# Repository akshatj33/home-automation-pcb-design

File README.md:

# home-automation-pcb-design
This is a board layout and schematic for home automation

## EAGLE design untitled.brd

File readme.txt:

This is a board layout and pcb design which I created for home automation on Eagle CAD platform.
It has 6 PWM pins to control the speed of 6 Fans and two shift registers to controll 16 lights.
The microcontroller used is ATMEGA328 which is basically arduino UNO.
The PCB has connections for bluetooth module so that the device can be controlled through a mobile app.

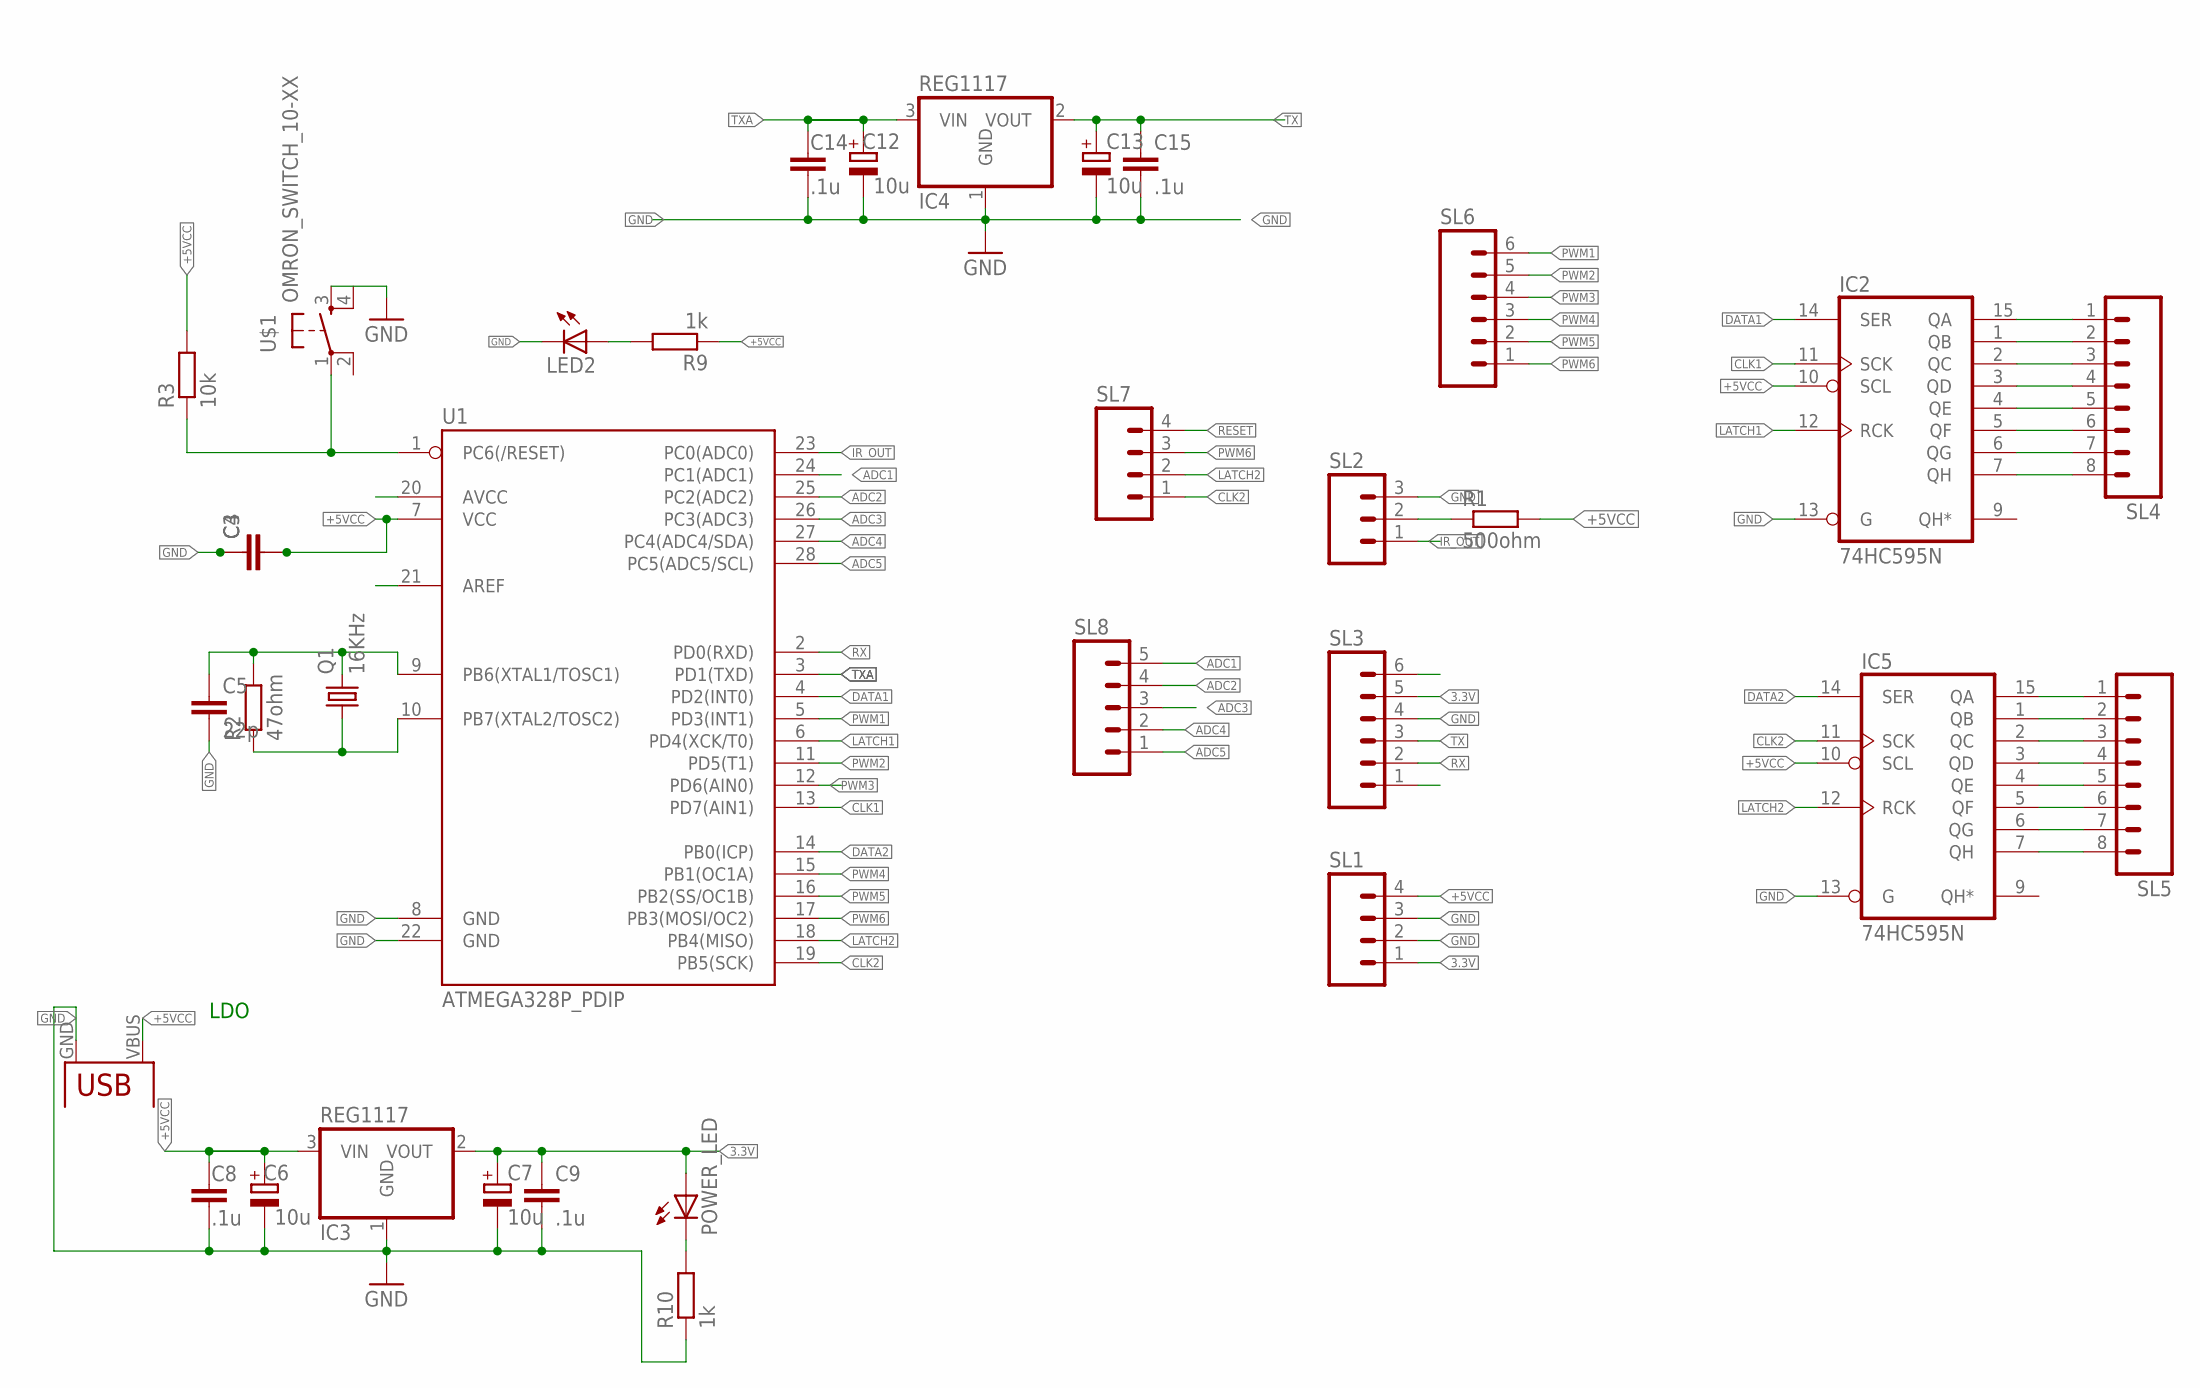
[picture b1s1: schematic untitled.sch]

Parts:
C3, C4: C-EU025-025X050; C025-025X050
C5: 22p; C025-025X050
C6, C7, C12, C13: 10u; E2,5-5
C8, C9, C14, C15: .1u; C025-025X050
IC2, IC5: 74HC595N; DIL16
IC3, IC4: REG1117; SOT223
LED2: LED3MM
POWER_LED: LED3MM
Q1: 16KHz; TC26H
R1: 500ohm; 0207/7
R2: 47ohm; 0207/7
R3: 10k; 0207/7
R9: 1k; 0207/10
R10: 1k; 0207/7
SL1, SL7: M04; 04P
SL2: M03; 03P
SL3, SL6: M06; 06P
SL4, SL5: M08; 08P
SL8: M05; 05P
U1: ATMEGA328P_PDIP; DIL28-3
U$1: OMRON_SWITCH_10-XX; B3F-10XX
U$2: USB(POWER)

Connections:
3.3V: C7.+, C9.1, IC3.2 (VOUT), POWER_LED.A, SL1.1, SL3.5
+5VCC: C3.2, C4.2, C6.+, C8.1, IC2.10 (SCL), IC3.3 (VIN), IC5.10 (SCL), R1.2, R3.2, R9.1, SL1.4, U1.7 (VCC), U$2.VBUS (VCC)
ADC1: SL8.5, U1.24 (PC1(ADC1))
ADC2: SL8.4, U1.25 (PC2(ADC2))
ADC3: SL8.3, U1.26 (PC3(ADC3))
ADC4: SL8.2, U1.27 (PC4(ADC4/SDA))
ADC5: SL8.1, U1.28 (PC5(ADC5/SCL))
CLK1: IC2.11 (SCK), U1.13 (PD7(AIN1))
CLK2: IC5.11 (SCK), SL7.1, U1.19 (PB5(SCK))
DATA1: IC2.14 (SER), U1.4 (PD2(INT0))
DATA2: IC5.14 (SER), U1.14 (PB0(ICP))
GND: C3.1, C4.1, C5.2, C6.-, C7.-, C8.2, C9.2, C12.-, C13.-, C14.2, C15.2, IC2.8 (GND), IC2.13 (G), IC3.1 (GND), IC4.1 (GND), IC5.8 (GND), IC5.13 (G), LED2.K (C), R10.1, SL1.2, SL1.3, SL2.3, SL3.4, U1.8 (GND), U1.22 (GND), U$1.3 (S), U$2.GND
IR_OUT: SL2.1, U1.23 (PC0(ADC0))
LATCH1: IC2.12 (RCK), U1.6 (PD4(XCK/T0))
LATCH2: IC5.12 (RCK), SL7.2, U1.18 (PB4(MISO))
unnamed: IC2.15 (QA), SL4.1
unnamed: R1.1, SL2.2
unnamed: LED2.A, R9.2
unnamed: IC2.1 (QB), SL4.2
unnamed: C5.1, Q1.2, R2.2, U1.9 (PB6(XTAL1/TOSC1))
unnamed: Q1.1, R2.1, U1.10 (PB7(XTAL2/TOSC2))
unnamed: POWER_LED.K (C), R10.2
unnamed: IC2.3 (QD), SL4.4
unnamed: IC2.2 (QC), SL4.3
unnamed: IC2.4 (QE), SL4.5
unnamed: IC2.5 (QF), SL4.6
unnamed: IC2.6 (QG), SL4.7
unnamed: IC2.7 (QH), SL4.8
unnamed: IC5.15 (QA), SL5.1
unnamed: IC5.1 (QB), SL5.2
unnamed: IC5.2 (QC), SL5.3
unnamed: IC5.3 (QD), SL5.4
unnamed: IC5.4 (QE), SL5.5
unnamed: IC5.5 (QF), SL5.6
unnamed: IC5.6 (QG), SL5.7
unnamed: IC5.7 (QH), SL5.8
PWM1: SL6.6, U1.5 (PD3(INT1))
PWM2: SL6.5, U1.11 (PD5(T1))
PWM3: SL6.4, U1.12 (PD6(AIN0))
PWM4: SL6.3, U1.15 (PB1(OC1A))
PWM5: SL6.2, U1.16 (PB2(SS/OC1B))
PWM6: SL6.1, SL7.3, U1.17 (PB3(MOSI/OC2))
RESET: R3.1, SL7.4, U1.1 (PC6(/RESET)), U$1.1
RX: SL3.2, U1.2 (PD0(RXD))
TX: C13.+, C15.1, IC4.2 (VOUT), SL3.3
TXA: C12.+, C14.1, IC4.3 (VIN), U1.3 (PD1(TXD))
VCC: IC2.16 (VCC), IC5.16 (VCC)

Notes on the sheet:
LDO

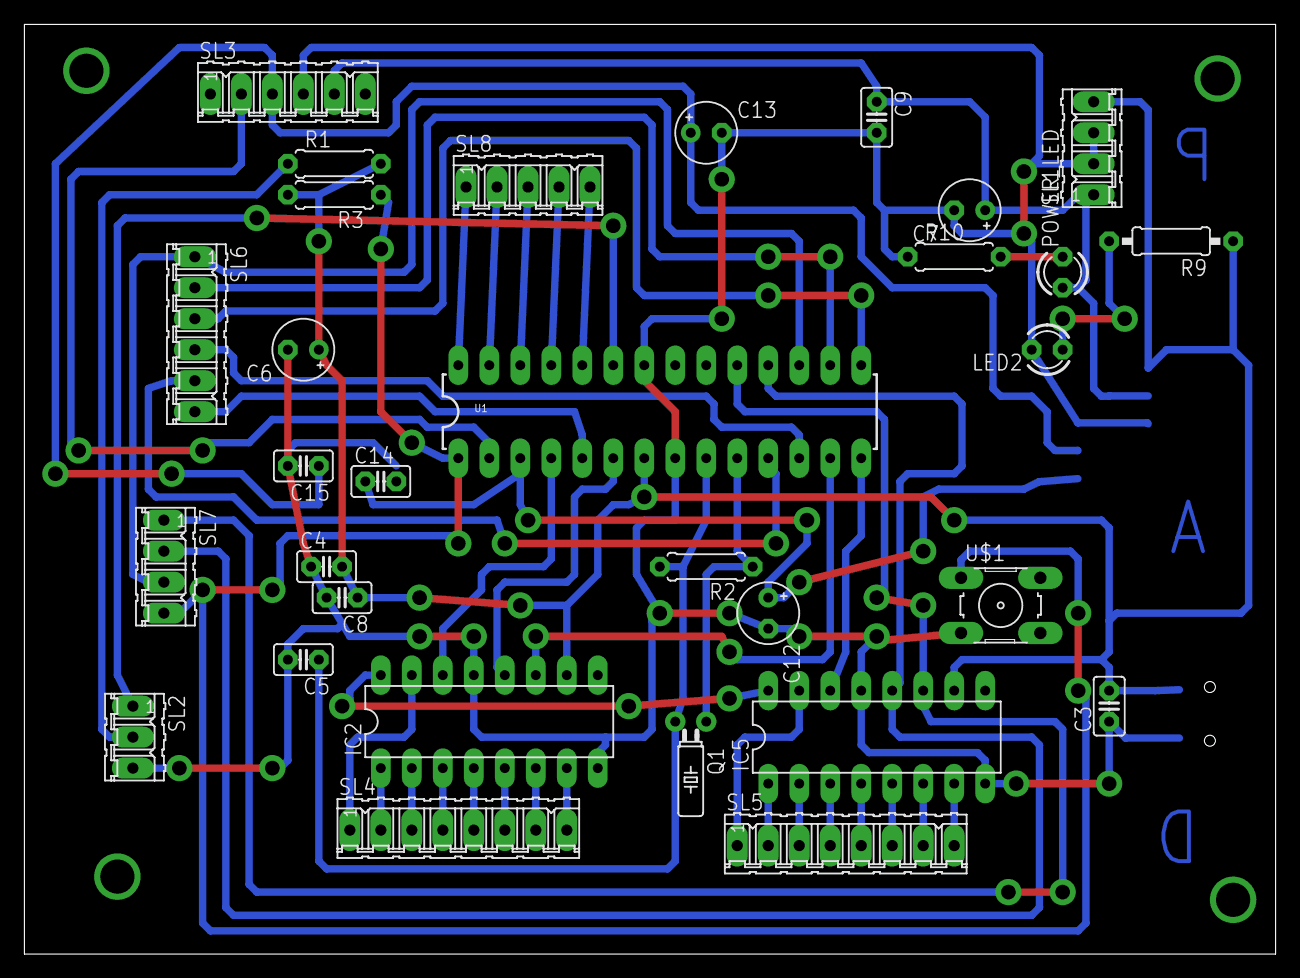
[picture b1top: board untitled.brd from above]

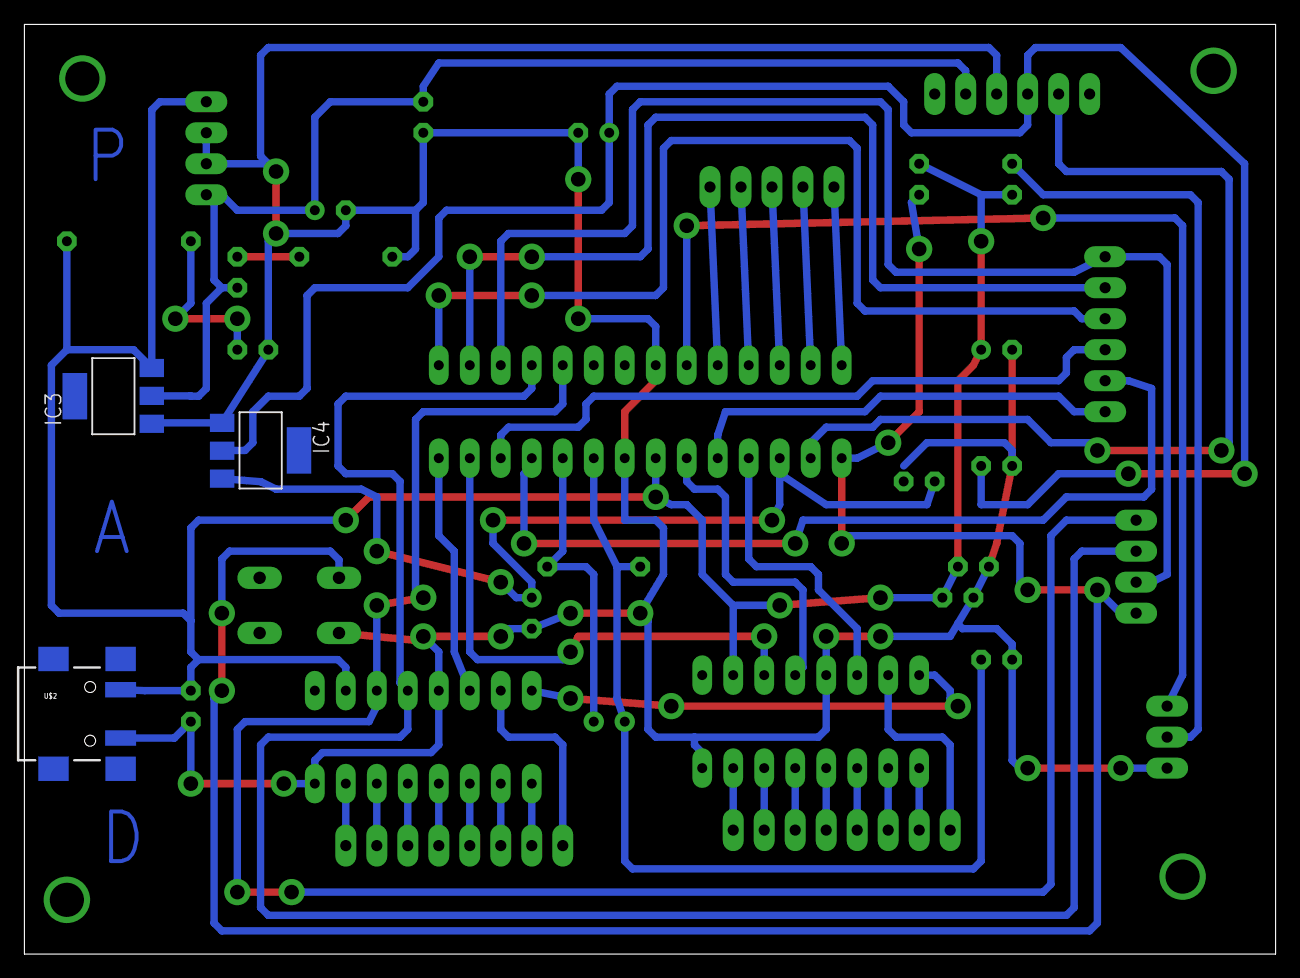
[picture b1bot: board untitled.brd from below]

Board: 2 copper layers, 102.5 x 76.2 mm, 34 parts (3 on the bottom side), 47 nets.

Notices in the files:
parts and their libraries:
SparkFun-DigitalIC: Licensing: Creative Commons ShareAlike 4.0 International - https://creativecommons.org/licenses/by-sa/4.0
